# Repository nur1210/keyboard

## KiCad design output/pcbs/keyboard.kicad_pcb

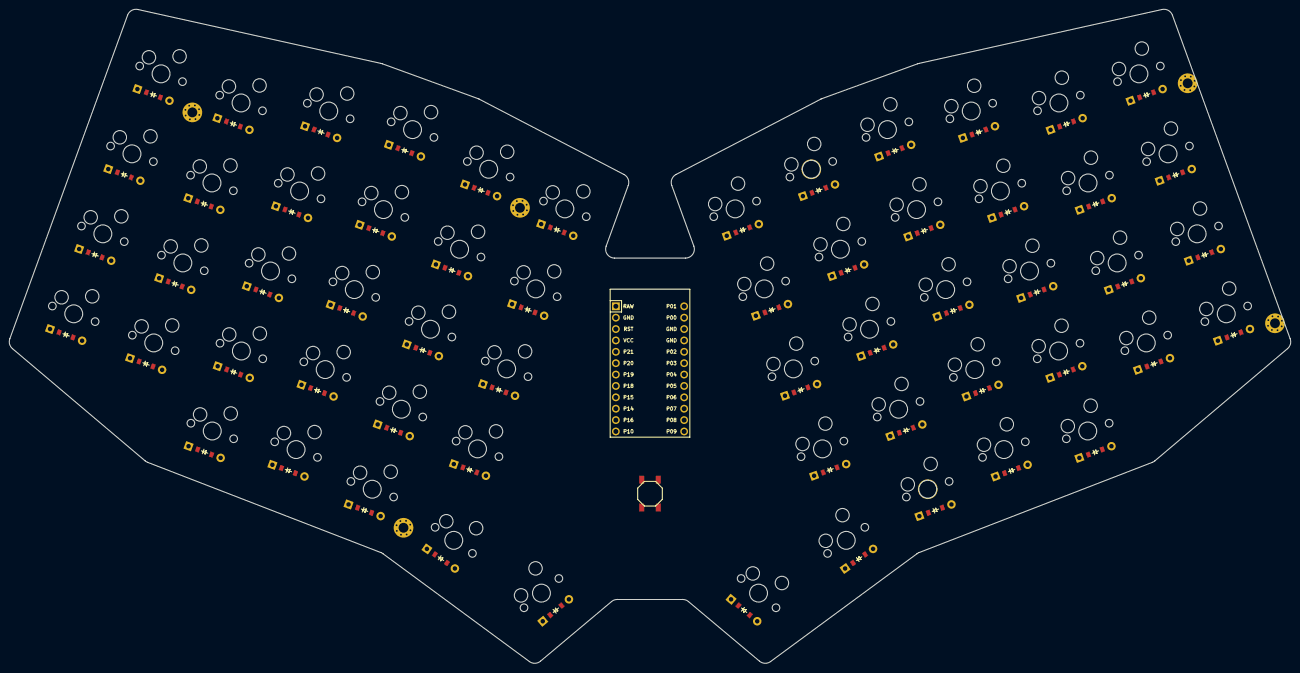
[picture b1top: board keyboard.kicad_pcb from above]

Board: 2 copper layers, 286.0 x 146.0 mm, 125 parts (0 on the bottom side), 76 nets, no tracks yet.

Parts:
B1: SW_TACT_ALPS_SKQGABE010
D1, D2, D3, D4, D5, D6, D7, D8, D9, D10, D11, D12, D13, D14, D15, D16, D17, D18, D19, D20, D21, D22, D23, D24, D25, D26, D27, D28, D29, D30, D31, D32, D33, D34, D35, D36, D37, D38, D39, D40, D41, D42, D43, D44, D45, D46, D47, D48, D49, D50, D51, D52, D53, D54, D55, D56, D57, D58: ComboDiode
MCU1: ProMicro
S1, S2, S3, S4, S5, S6, S7, S8, S9, S10, S11, S12, S13, S14, S15, S16, S17, S18, S19, S20, S21, S22, S23, S24, S25, S26, S27, S28, S29, S30, S31, S32, S33, S34, S35, S36, S37, S38, S39, S40, S41, S42, S43, S44, S45, S46, S47, S48, S49, S50, S51, S52, S53, S54, S55, S56, S57, S58: MX
_1, _2, _3, _4, _5, _6, _7: MountingHole_2.2mm_M2_Pad_Via

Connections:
GND: B1.1, MCU1.2, MCU1.15, MCU1.16
P0: D32.1, D36.1, D41.1, D46.1, D51.1, D55.1, MCU1.14
P1: D33.1, D37.1, D42.1, D47.1, D52.1, D56.1, MCU1.13
P4: D31.1, D35.1, D40.1, D45.1, D50.1, D54.1, MCU1.19
P5: D30.1, D34.1, D39.1, D44.1, D49.1, D53.1, MCU1.20
P6: D38.1, D43.1, D48.1, D57.1, D58.1, MCU1.21
P7: MCU1.22, S15.1, S16.1, S17.1, S18.1, S19.1, S44.1, S45.1, S46.1, S47.1, S48.1
P8: MCU1.23, S20.1, S21.1, S22.1, S23.1, S28.1, S49.1, S50.1, S51.1, S52.1, S57.1
P9: MCU1.24, S24.1, S25.1, S26.1, S27.1, S29.1, S53.1, S54.1, S55.1, S56.1, S58.1
P10: MCU1.12, S10.1, S11.1, S12.1, S13.1, S14.1, S39.1, S40.1, S41.1, S42.1, S43.1
P14: MCU1.10, S1.1, S2.1, S3.1, S4.1, S30.1, S31.1, S32.1, S33.1
P15: D9.1, D14.1, D19.1, D28.1, D29.1, MCU1.9
P16: MCU1.11, S5.1, S6.1, S7.1, S8.1, S9.1, S34.1, S35.1, S36.1, S37.1, S38.1
P18: D1.1, D5.1, D10.1, D15.1, D20.1, D24.1, MCU1.8
P19: D2.1, D6.1, D11.1, D16.1, D21.1, D25.1, MCU1.7
P20: D3.1, D7.1, D12.1, D17.1, D22.1, D26.1, MCU1.6
P21: D4.1, D8.1, D13.1, D18.1, D23.1, D27.1, MCU1.5
RST: B1.2, MCU1.3
index_bottom: D20.2, S20.2
index_home: D21.2, S21.2
index_mod: D19.2, S19.2
index_num: D23.2, S23.2
index_top: D22.2, S22.2
inner_bottom: D24.2, S24.2
inner_home: D25.2, S25.2
inner_num: D27.2, S27.2
inner_top: D26.2, S26.2
layer_cluster: D28.2, S28.2
middle_bottom: D15.2, S15.2
middle_home: D16.2, S16.2
middle_mod: D14.2, S14.2
middle_num: D18.2, S18.2
middle_top: D17.2, S17.2
mirror_index_bottom: D49.2, S49.2
mirror_index_home: D50.2, S50.2
mirror_index_mod: D48.2, S48.2
mirror_index_num: D52.2, S52.2
mirror_index_top: D51.2, S51.2
mirror_inner_bottom: D53.2, S53.2
mirror_inner_home: D54.2, S54.2
mirror_inner_num: D56.2, S56.2
mirror_inner_top: D55.2, S55.2
mirror_layer_cluster: D57.2, S57.2
mirror_middle_bottom: D44.2, S44.2
mirror_middle_home: D45.2, S45.2
mirror_middle_mod: D43.2, S43.2
mirror_middle_num: D47.2, S47.2
mirror_middle_top: D46.2, S46.2
mirror_outer_bottom: D30.2, S30.2
mirror_outer_home: D31.2, S31.2
mirror_outer_num: D33.2, S33.2
mirror_outer_top: D32.2, S32.2
mirror_pinky_bottom: D34.2, S34.2
mirror_pinky_home: D35.2, S35.2
mirror_pinky_num: D37.2, S37.2
mirror_pinky_top: D36.2, S36.2
mirror_ring_bottom: D39.2, S39.2
mirror_ring_home: D40.2, S40.2
mirror_ring_mod: D38.2, S38.2
mirror_ring_num: D42.2, S42.2
mirror_ring_top: D41.2, S41.2
mirror_space_cluster: D58.2, S58.2
outer_bottom: D1.2, S1.2
outer_home: D2.2, S2.2
outer_num: D4.2, S4.2
outer_top: D3.2, S3.2
pinky_bottom: D5.2, S5.2
pinky_home: D6.2, S6.2
pinky_num: D8.2, S8.2
pinky_top: D7.2, S7.2
ring_bottom: D10.2, S10.2
ring_home: D11.2, S11.2
ring_mod: D9.2, S9.2
ring_num: D13.2, S13.2
ring_top: D12.2, S12.2
space_cluster: D29.2, S29.2
